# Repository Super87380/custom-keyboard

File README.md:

# Custom 75% Mechanical Keyboard

This is a custom 75% mechanical keyboard with 3 macro keys that I designed every part for, from the PCB to the firmware.

## Why I Built it
A while before finding out about Hack Club I wanted to make my own mechanical keyboard. After finding out how much it would cost I got de motivated and gave up on the idea.
Later I was watching YouTube when the creator mentioned Hack Club and how they help teenagers get experience in engineering. I was looking through the programs running when I saw KEEB.
With the opportunity to get the keyboard funded by Hack Club/KEEB it was the perfect chance for me to make the keyboard I had wanted to before.

## Features
- 3 Macro keys
- Rotary Encoder with a switch
- RGB back lighting
- Vast firmware support - the firmware I made uses KMK

## Designing
I started this project by brainstorming ideas for different layouts, sizes, and features. My original idea was a 75% keyboard with a screen, 1 macro key, and a rotary encoder. The idea soon evolved into what it is now.
After brainstorming I used [keyboard layout editor](https://www.keyboard-layout-editor.com/) and [photopea](https://www.photopea.com/) to design the layout and matrix wiring digitally.
I then made the first schematic and PCB in KiCad with a screen and 1 macro key. After I finished the schematic and PCB I realized I wanted to add backlighting for late night gaming/programming sessions and more macro keys, so I added sk6812 mini-e LED's under each switch and removed the screen for 2 more macro keys. After I finished with the electronics I designed a case and plate in Onshape, I found this pretty challenging as it was my first time using Onshape; I can definitely improve the case a lot. I then made the firmware, I chose to sue KMK because I have more expierence with python and have made a macropad with KMK already.

## What I Found Difficult
- LED wiring, especially because I didnt originally route with them in minde
- Modeling the case and plate in Onshape
- Sourcing cheap components with cheap shipping

## What I Learned
- Modelling in Onshape
- Better PCB design
- How mechanical keyboards work
- Reading data sheets and applying what I read
- Layers in KMK
- RGB in KMK

## BOM
| Sl No. | Name | Notes | Quantity | Price Per Unit | Cost | Shipping | Link |
| :---: | :--- | :--- | :---: | :---: | :---: | :---: | :--- |
| 1 | PCB | Manufactured by JLCPBC (minimum 5, order through JLclone desktop app - saves money) | 1 | $25.50 | $25.50 | $15.00 | [JLCPCB](JLCPCB) |
| 2 | Diode (1N4148) | Diodes to prevent ghosting (need 84, minimum 100) | 100 | $0.0295 | $2.95 | $13.54 | [LCSC](https://www.lcsc.com/product-detail/C258182.html) |
| 3 | Resistor (0805W8F5600T5E) | For start and end of LED data signals (only need 2, minimum of 100) | 100 | $0.0028 | $0.28 | Included* | [LCSC](https://www.lcsc.com/product-detail/C28636.html) |
| 4 | Capacitor (CC0603KRX7R7BB104) | Decoupling capacitors for LED's (need 83, multiples of 50) | 100 | $0.0142 | $1.42 | Included* | [LCSC](https://www.lcsc.com/product-detail/C108079.html?s_z=n_q_CC0603KRX7R7BB104) |
| 5 | LED (SK6812MINI-E) | LED's for backglow of the keyboard (order in multiples of 5) | 85 | $0.0651 | $5.53 | Included* | [LCSC](https://www.lcsc.com/product-detail/C5149201.html?s_z=n_SK6812%2520MINI-E) |
| 6 | Raspberry Pi Pico W (with headers) | The microcontroller for the keyboard (already owned) | 1 | $0.00 | $0.00 | $0.00 | [PiShop](https://www.pishop.ca/product/raspberry-pi-pico-w/) |
| 7 | Switches | Mechanical keyboard switches (pack of 100) | 100 | $0.20 | $20.00 | $0.00 | [Amazon](https://www.amazon.com/dp/B0CX8X1X7P) |
| 8 | Keycaps | Keycaps for the switches | 1 | $10.09 | $10.09 | $0.00 | [AliExpress](https://www.aliexpress.com/item/1005009162201589.html) |
| 9 | Rotary Encoder | Rotary encoder for volume and play/pause media (already owned) | 1 | $0.00 | $0.00 | $0.00 | [DigiKey](https://www.digikey.ca/en/products/detail/bourns-inc/PEC11R-4220F-S0012/4499661) |
| 10 | Rotary Encoder Knob | Knob for the rotary encoder, 3D printed | 1 | $0.00 | $0.00 | $0.00 | — |
| 11 | Case + plate | 3D printed | 1 | $0.00 | $0.00 | $0.00 | — |
| 12 | Stabilizers | 7x 2u, 1x 6.25u | 1 | $12.05 | $12.05 | $0.00 | [Walmart](https://www.walmart.ca/en/ip/Mechanical-Keyboard-Cherry-Mx-Switch-Pcb-Mounted-Cherry-Stabilizer-Clear-Transparent-Case-6-25U-Modifier-Key-Stabiliser/7HYKUIE7RG06) |
| 13 | USB C Cable | Aviation style, coiled | 1 | $7.56 | $7.56 | $0.00 | [Amazon](https://www.amazon.ca/Coiled-Keyboards-Aviation-Mechanical-70-87inch/dp/B0GYD7GZT2) |
| 14 | Type C to Micro USB | For connecting the USB C cable to the pico | 1 | $1.78 | $1.78 | $0.00 | [Amazon](https://www.amazon.ca/dp/B0D8ZSWC1D) |

> **Additional Notes:** Items from Amazon may have shipping charges; Amazon Prime is used so shipping costs are not included. 
> 
> All LCSC items share a combined shipping fee of **$13.54 USD**. PCB shipping is estimated at **$15.00 USD**. Total shipping: **$28.54 USD**.

- **Sub Total:** $87.16 USD
- **Shipping Total:** $28.54 USD
- **Total USD:** $115.70 USD

## Files
[PCB](PCB)
[CAD](CAD)
[Firmware](Firmware)
[Journal](JOURNAL.md)
[BOM](BOM)

## Credits
This was made possible through the funding of Hack Club and KEEB, opensource firmware and software, everyone who helped with my questions in the slack, 3D models from grabcad, tutorials on YouTube, and inspiration from other KEEB github repos.

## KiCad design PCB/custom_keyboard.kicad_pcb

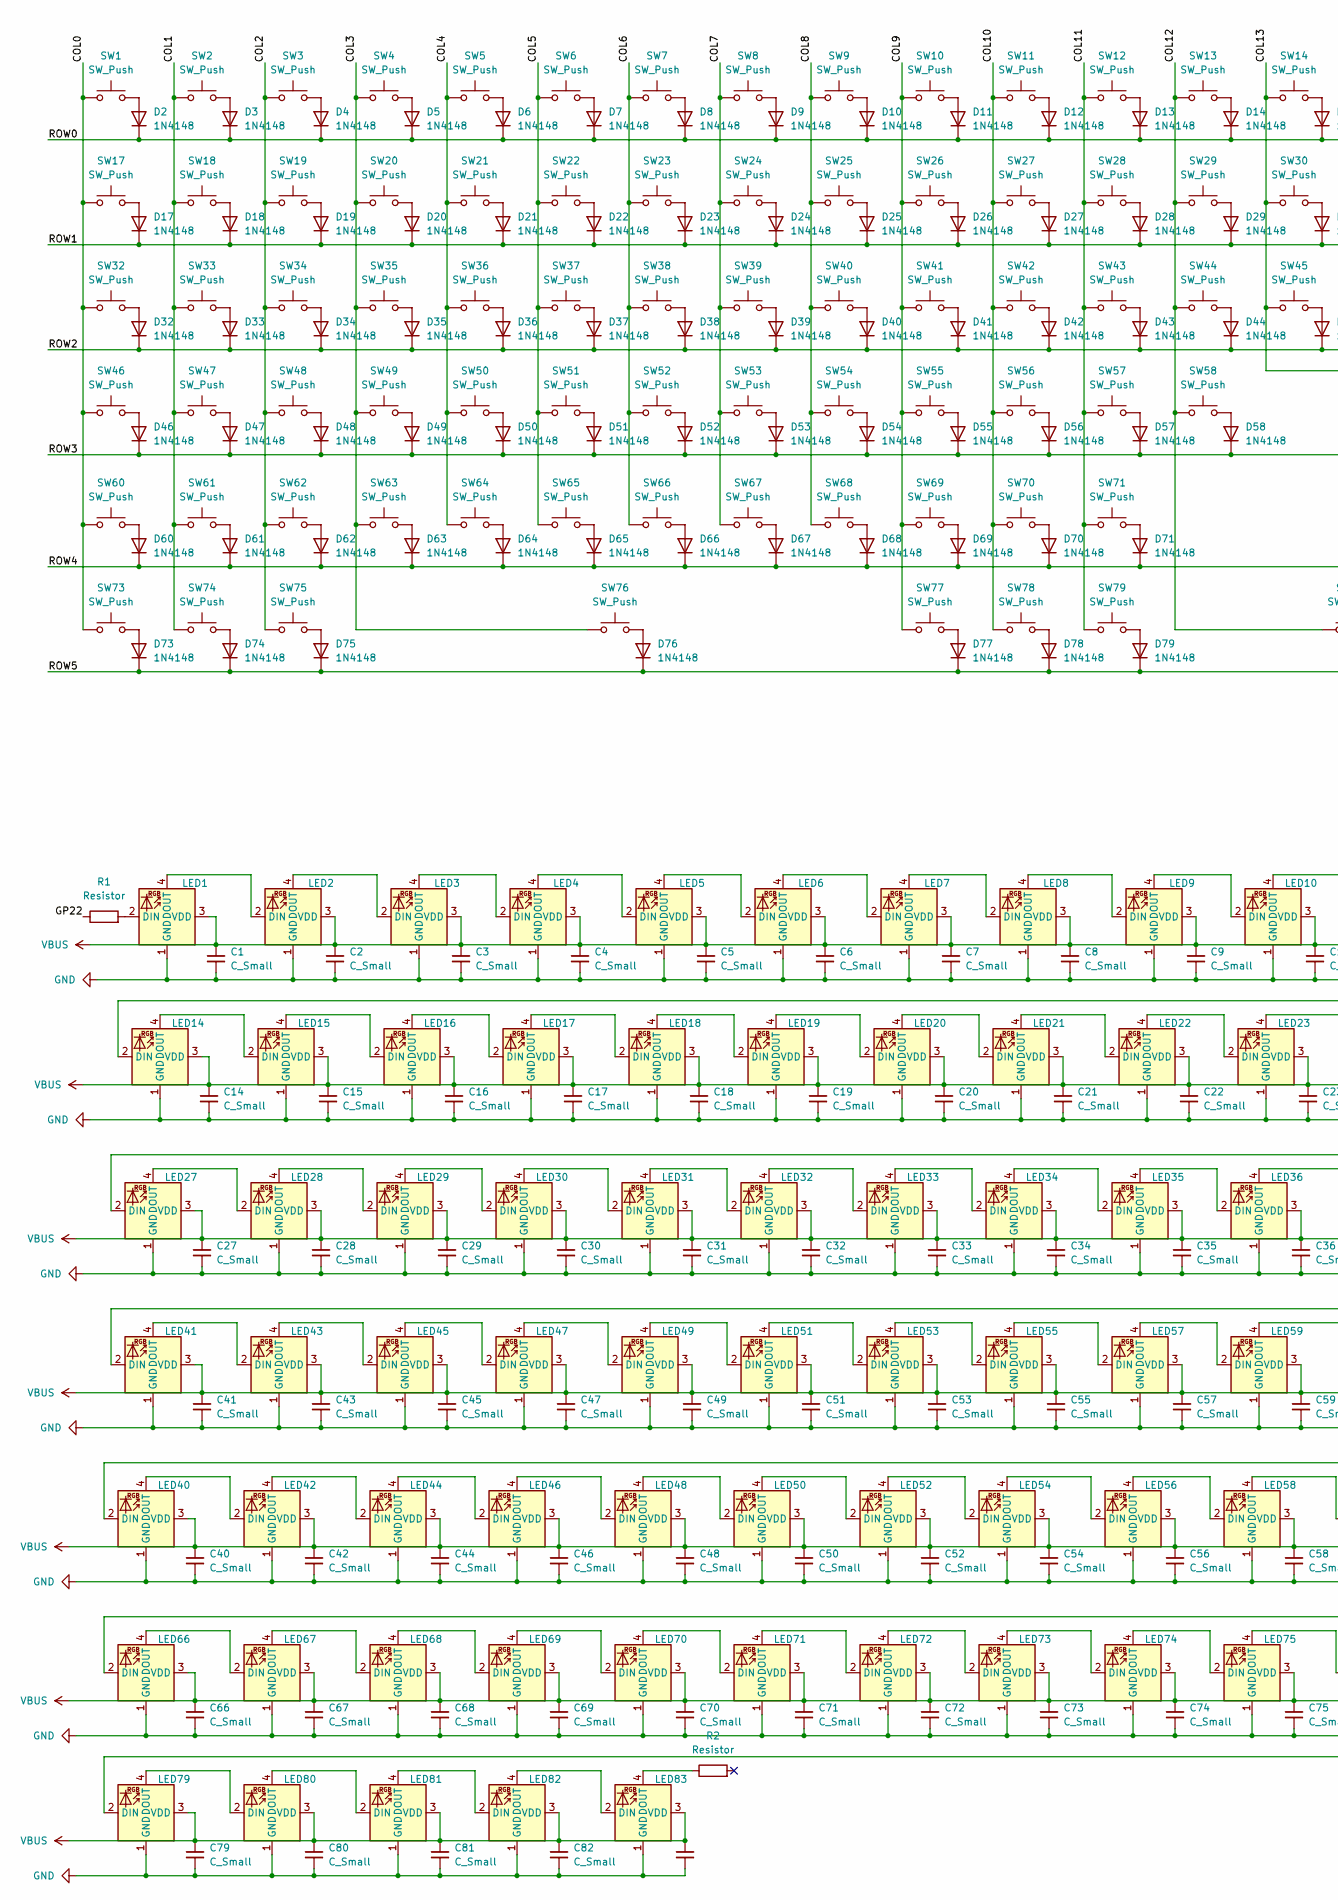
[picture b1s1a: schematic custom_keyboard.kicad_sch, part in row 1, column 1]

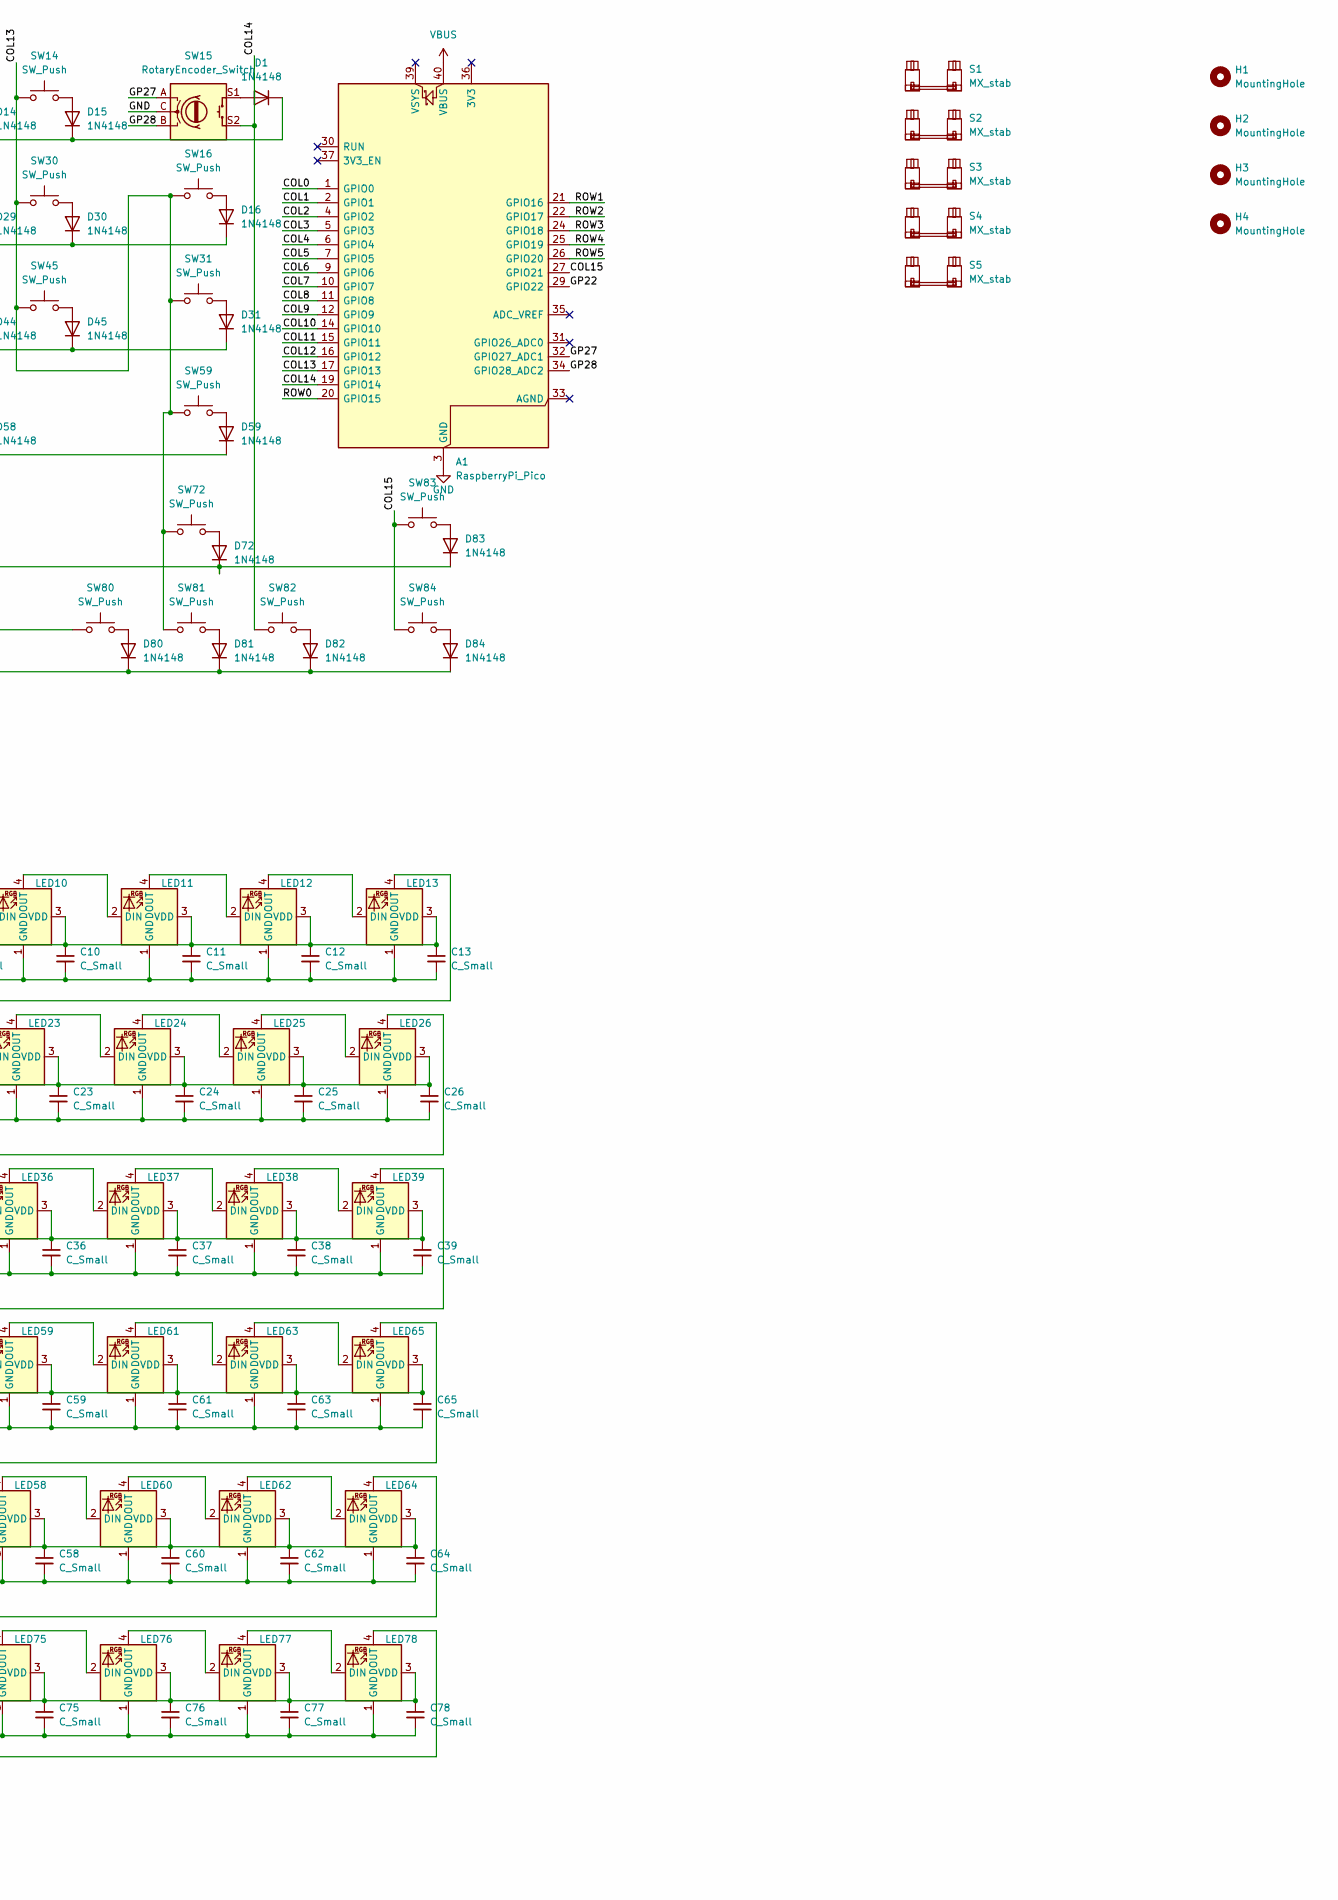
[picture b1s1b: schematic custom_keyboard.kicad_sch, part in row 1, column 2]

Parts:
A1: RaspberryPi_Pico; RaspberryPi_Pico_Common_THT
C1, C2, C3, C4, C5, C6, C7, C8, C9, C10, C11, C12, C13, C14, C15, C16, C17, C18, C19, C20, C21, C22, C23, C24, C25, C26, C27, C28, C29, C30, C31, C32, C33, C34, C35, C36, C37, C38, C39, C40, C41, C42, C43, C44, C45, C46, C47, C48, C49, C50, C51, C52, C53, C54, C55, C56, C57, C58, C59, C60, C61, C62, C63, C64, C65, C66, C67, C68, C69, C70, C71, C72, C73, C74, C75, C76, C77, C78, C79, C80, C81, C82, C83: C_Small; C_0603_1608Metric_Pad1.08x0.95mm_HandSolder
D1, D2, D3, D4, D5, D6, D7, D8, D9, D10, D11, D12, D13, D14, D15, D16, D17, D18, D19, D20, D21, D22, D23, D24, D25, D26, D27, D28, D29, D30, D31, D32, D33, D34, D35, D36, D37, D38, D39, D40, D41, D42, D43, D44, D45, D46, D47, D48, D49, D50, D51, D52, D53, D54, D55, D56, D57, D58, D59, D60, D61, D62, D63, D64, D65, D66, D67, D68, D69, D70, D71, D72, D73, D74, D75, D76, D77, D78, D79, D80, D81, D82, D83, D84: 1N4148; D_DO-35_SOD27_P7.62mm_Horizontal
H1, H2, H3, H4: MountingHole; MountingHole_3.2mm_M3_DIN965_Pad_TopBottom
LED1, LED2, LED3, LED4, LED5, LED6, LED7, LED8, LED9, LED10, LED11, LED12, LED13, LED14, LED15, LED16, LED17, LED18, LED19, LED20, LED21, LED22, LED23, LED24, LED25, LED26, LED27, LED28, LED29, LED30, LED31, LED32, LED33, LED34, LED35, LED36, LED37, LED38, LED39, LED40, LED41, LED42, LED43, LED44, LED45, LED46, LED47, LED48, LED49, LED50, LED51, LED52, LED53, LED54, LED55, LED56, LED57, LED58, LED59, LED60, LED61, LED62, LED63, LED64, LED65, LED66, LED67, LED68, LED69, LED70, LED71, LED72, LED73, LED74, LED75, LED76, LED77, LED78, LED79, LED80, LED81, LED82, LED83: MX_SK6812MINI-E_LCSC; LED_MX_6028R_1
R1, R2: Resistor; R_0805_2012Metric
S1: MX_stab; STAB_MX_2.75u_MODEL
S2, S5: MX_stab; STAB_MX_2.25u_MODEL
S3: MX_stab; STAB_MX_2u_MODEL
S4: MX_stab; STAB_MX_6.25u_MODEL
SW1, SW2, SW3, SW4, SW5, SW6, SW7, SW8, SW9, SW10, SW11, SW12, SW13, SW16, SW17, SW18, SW19, SW20, SW21, SW22, SW23, SW24, SW25, SW26, SW27, SW28, SW29, SW30, SW31, SW33, SW34, SW35, SW36, SW37, SW38, SW39, SW40, SW41, SW42, SW43, SW44, SW47, SW48, SW49, SW50, SW51, SW52, SW53, SW54, SW55, SW56, SW57, SW58, SW59, SW60, SW61, SW62, SW63, SW64, SW65, SW66, SW67, SW68, SW69, SW70, SW71, SW72, SW80, SW81, SW82, SW83, SW84: SW_Push; SW_MX_1u_MODEL
SW14, SW73, SW74, SW75, SW76, SW77, SW78: SW_Push; SW_MX_1.25u_MODEL
SW15: RotaryEncoder_Switch; ROT_Alps_EC11E-Switch
SW32, SW45, SW79: SW_Push; SW_MX_1.5u_MODEL
SW46: SW_Push; SW_MX_1.75u_MODEL

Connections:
/COL0: A1.1 (GPIO0), SW1.1, SW17.1, SW32.1, SW46.1, SW60.1, SW73.1
/COL1: A1.2 (GPIO1), SW2.1, SW18.1, SW33.1, SW47.1, SW61.1, SW74.1
/COL2: A1.4 (GPIO2), SW3.1, SW19.1, SW34.1, SW48.1, SW62.1, SW75.1
/COL3: A1.5 (GPIO3), SW4.1, SW20.1, SW35.1, SW49.1, SW63.1, SW76.1
/COL4: A1.6 (GPIO4), SW5.1, SW21.1, SW36.1, SW50.1, SW64.1
/COL5: A1.7 (GPIO5), SW6.1, SW22.1, SW37.1, SW51.1, SW65.1
/COL6: A1.9 (GPIO6), SW7.1, SW23.1, SW38.1, SW52.1, SW66.1
/COL7: A1.10 (GPIO7), SW8.1, SW24.1, SW39.1, SW53.1, SW67.1
/COL8: A1.11 (GPIO8), SW9.1, SW25.1, SW40.1, SW54.1, SW68.1
/COL9: A1.12 (GPIO9), SW10.1, SW26.1, SW41.1, SW55.1, SW69.1, SW77.1
/COL10: A1.14 (GPIO10), SW11.1, SW27.1, SW42.1, SW56.1, SW70.1, SW78.1
/COL11: A1.15 (GPIO11), SW12.1, SW28.1, SW43.1, SW57.1, SW71.1, SW79.1
/COL12: A1.16 (GPIO12), SW13.1, SW29.1, SW44.1, SW58.1, SW80.1
/COL13: A1.17 (GPIO13), SW14.1, SW16.1, SW30.1, SW31.1, SW45.1, SW59.1, SW72.1, SW81.1
/COL14: A1.19 (GPIO14), SW15.S2, SW82.1
/COL15: A1.27 (GPIO21), SW83.1, SW84.1
/GP22: A1.29 (GPIO22), R1.1
/GP27: A1.32 (GPIO27_ADC1), SW15.A
/GP28: A1.34 (GPIO28_ADC2), SW15.B
/ROW0: A1.20 (GPIO15), D1.1 (K), D2.1 (K), D3.1 (K), D4.1 (K), D5.1 (K), D6.1 (K), D7.1 (K), D8.1 (K), D9.1 (K), D10.1 (K), D11.1 (K), D12.1 (K), D13.1 (K), D14.1 (K), D15.1 (K)
/ROW1: A1.21 (GPIO16), D16.1 (K), D17.1 (K), D18.1 (K), D19.1 (K), D20.1 (K), D21.1 (K), D22.1 (K), D23.1 (K), D24.1 (K), D25.1 (K), D26.1 (K), D27.1 (K), D28.1 (K), D29.1 (K), D30.1 (K)
/ROW2: A1.22 (GPIO17), D31.1 (K), D32.1 (K), D33.1 (K), D34.1 (K), D35.1 (K), D36.1 (K), D37.1 (K), D38.1 (K), D39.1 (K), D40.1 (K), D41.1 (K), D42.1 (K), D43.1 (K), D44.1 (K), D45.1 (K)
/ROW3: A1.24 (GPIO18), D46.1 (K), D47.1 (K), D48.1 (K), D49.1 (K), D50.1 (K), D51.1 (K), D52.1 (K), D53.1 (K), D54.1 (K), D55.1 (K), D56.1 (K), D57.1 (K), D58.1 (K), D59.1 (K)
/ROW4: A1.25 (GPIO19), D60.1 (K), D61.1 (K), D62.1 (K), D63.1 (K), D64.1 (K), D65.1 (K), D66.1 (K), D67.1 (K), D68.1 (K), D69.1 (K), D70.1 (K), D71.1 (K), D72.1 (K), D83.1 (K)
/ROW5: A1.26 (GPIO20), D73.1 (K), D74.1 (K), D75.1 (K), D76.1 (K), D77.1 (K), D78.1 (K), D79.1 (K), D80.1 (K), D81.1 (K), D82.1 (K), D84.1 (K)
GND: A1.3 (GND), A1.8 (GND), A1.13 (GND), A1.18 (GND), A1.23 (GND), A1.28 (GND), A1.38 (GND), C1.2, C2.2, C3.2, C4.2, C5.2, C6.2, C7.2, C8.2, C9.2, C10.2, C11.2, C12.2, C13.2, C14.2, C15.2, C16.2, C17.2, C18.2, C19.2, C20.2, C21.2, C22.2, C23.2, C24.2, C25.2, C26.2, C27.2, C28.2, C29.2, C30.2, C31.2, C32.2, C33.2, C34.2, C35.2, C36.2, C37.2, C38.2, C39.2, C40.2, C41.2, C42.2, C43.2, C44.2, C45.2, C46.2, C47.2, C48.2, C49.2, C50.2, C51.2, C52.2, C53.2, C54.2, C55.2, C56.2, C57.2, C58.2, C59.2, C60.2, C61.2, C62.2, C63.2, C64.2, C65.2, C66.2, C67.2, C68.2, C69.2, C70.2, C71.2, C72.2, C73.2, C74.2, C75.2, C76.2, C77.2, C78.2, C79.2, C80.2, C81.2, C82.2, C83.2, LED1.1 (GND), LED2.1 (GND), LED3.1 (GND), LED4.1 (GND), LED5.1 (GND), LED6.1 (GND), LED7.1 (GND), LED8.1 (GND), LED9.1 (GND), LED10.1 (GND), LED11.1 (GND), LED12.1 (GND), LED13.1 (GND), LED14.1 (GND), LED15.1 (GND), LED16.1 (GND), LED17.1 (GND), LED18.1 (GND), LED19.1 (GND), LED20.1 (GND), LED21.1 (GND), LED22.1 (GND), LED23.1 (GND), LED24.1 (GND), LED25.1 (GND), LED26.1 (GND), LED27.1 (GND), LED28.1 (GND), LED29.1 (GND), LED30.1 (GND), LED31.1 (GND), LED32.1 (GND), LED33.1 (GND), LED34.1 (GND), LED35.1 (GND), LED36.1 (GND), LED37.1 (GND), LED38.1 (GND), LED39.1 (GND), LED40.1 (GND), LED41.1 (GND), LED42.1 (GND), LED43.1 (GND), LED44.1 (GND), LED45.1 (GND), LED46.1 (GND), LED47.1 (GND), LED48.1 (GND), LED49.1 (GND), LED50.1 (GND), LED51.1 (GND), LED52.1 (GND), LED53.1 (GND), LED54.1 (GND), LED55.1 (GND), LED56.1 (GND), LED57.1 (GND), LED58.1 (GND), LED59.1 (GND), LED60.1 (GND), LED61.1 (GND), LED62.1 (GND), LED63.1 (GND), LED64.1 (GND), LED65.1 (GND), LED66.1 (GND), LED67.1 (GND), LED68.1 (GND), LED69.1 (GND), LED70.1 (GND), LED71.1 (GND), LED72.1 (GND), LED73.1 (GND), LED74.1 (GND), LED75.1 (GND), LED76.1 (GND), LED77.1 (GND), LED78.1 (GND), LED79.1 (GND), LED80.1 (GND), LED81.1 (GND), LED82.1 (GND), LED83.1 (GND), SW15.C
unnamed: D1.2 (A), SW15.S1
unnamed: D2.2 (A), SW1.2
unnamed: D3.2 (A), SW2.2
unnamed: D4.2 (A), SW3.2
unnamed: D5.2 (A), SW4.2
unnamed: D6.2 (A), SW5.2
unnamed: D7.2 (A), SW6.2
unnamed: D8.2 (A), SW7.2
unnamed: D9.2 (A), SW8.2
unnamed: D10.2 (A), SW9.2
unnamed: D11.2 (A), SW10.2
unnamed: D12.2 (A), SW11.2
unnamed: D13.2 (A), SW12.2
unnamed: D14.2 (A), SW13.2
unnamed: D15.2 (A), SW14.2
unnamed: D16.2 (A), SW16.2
unnamed: D17.2 (A), SW17.2
unnamed: D18.2 (A), SW18.2
unnamed: D19.2 (A), SW19.2
unnamed: D20.2 (A), SW20.2
unnamed: D21.2 (A), SW21.2
unnamed: D22.2 (A), SW22.2
unnamed: D23.2 (A), SW23.2
unnamed: D24.2 (A), SW24.2
unnamed: D25.2 (A), SW25.2
unnamed: D26.2 (A), SW26.2
unnamed: D27.2 (A), SW27.2
unnamed: D28.2 (A), SW28.2
unnamed: D29.2 (A), SW29.2
unnamed: D30.2 (A), SW30.2
unnamed: D31.2 (A), SW31.2
unnamed: D32.2 (A), SW32.2
unnamed: D33.2 (A), SW33.2
unnamed: D34.2 (A), SW34.2
unnamed: D35.2 (A), SW35.2
unnamed: D36.2 (A), SW36.2
unnamed: D37.2 (A), SW37.2
unnamed: D38.2 (A), SW38.2
unnamed: D39.2 (A), SW39.2
unnamed: D40.2 (A), SW40.2
unnamed: D41.2 (A), SW41.2
unnamed: D42.2 (A), SW42.2
unnamed: D43.2 (A), SW43.2
unnamed: D44.2 (A), SW44.2
unnamed: D45.2 (A), SW45.2
unnamed: D46.2 (A), SW46.2
unnamed: D47.2 (A), SW47.2
unnamed: D48.2 (A), SW48.2
unnamed: D49.2 (A), SW49.2
unnamed: D50.2 (A), SW50.2
unnamed: D51.2 (A), SW51.2
unnamed: D52.2 (A), SW52.2
unnamed: D53.2 (A), SW53.2
unnamed: D54.2 (A), SW54.2
unnamed: D55.2 (A), SW55.2
unnamed: D56.2 (A), SW56.2
unnamed: D57.2 (A), SW57.2
unnamed: D58.2 (A), SW58.2
unnamed: D59.2 (A), SW59.2
unnamed: D60.2 (A), SW60.2
unnamed: D61.2 (A), SW61.2
unnamed: D62.2 (A), SW62.2
unnamed: D63.2 (A), SW63.2
unnamed: D64.2 (A), SW64.2
unnamed: D65.2 (A), SW65.2
unnamed: D66.2 (A), SW66.2
unnamed: D67.2 (A), SW67.2
unnamed: D68.2 (A), SW68.2
unnamed: D69.2 (A), SW69.2
unnamed: D70.2 (A), SW70.2
unnamed: D71.2 (A), SW71.2
unnamed: D72.2 (A), SW72.2
unnamed: D73.2 (A), SW73.2
unnamed: D74.2 (A), SW74.2
unnamed: D75.2 (A), SW75.2
unnamed: D76.2 (A), SW76.2
unnamed: D77.2 (A), SW77.2
unnamed: D78.2 (A), SW78.2
unnamed: D79.2 (A), SW79.2
unnamed: D80.2 (A), SW80.2
unnamed: D81.2 (A), SW81.2
unnamed: D82.2 (A), SW82.2
unnamed: D83.2 (A), SW83.2
unnamed: D84.2 (A), SW84.2
unnamed: LED1.2 (DIN), R1.2
unnamed: LED1.4 (DOUT), LED2.2 (DIN)
unnamed: LED2.4 (DOUT), LED3.2 (DIN)
unnamed: LED3.4 (DOUT), LED4.2 (DIN)
unnamed: LED4.4 (DOUT), LED5.2 (DIN)
unnamed: LED5.4 (DOUT), LED6.2 (DIN)
unnamed: LED6.4 (DOUT), LED7.2 (DIN)
unnamed: LED7.4 (DOUT), LED8.2 (DIN)
unnamed: LED8.4 (DOUT), LED9.2 (DIN)
unnamed: LED9.4 (DOUT), LED10.2 (DIN)
unnamed: LED10.4 (DOUT), LED11.2 (DIN)
unnamed: LED11.4 (DOUT), LED12.2 (DIN)
unnamed: LED12.4 (DOUT), LED13.2 (DIN)
unnamed: LED13.4 (DOUT), LED14.2 (DIN)
unnamed: LED14.4 (DOUT), LED15.2 (DIN)
unnamed: LED15.4 (DOUT), LED16.2 (DIN)
unnamed: LED16.4 (DOUT), LED17.2 (DIN)
unnamed: LED17.4 (DOUT), LED18.2 (DIN)
unnamed: LED18.4 (DOUT), LED19.2 (DIN)
unnamed: LED19.4 (DOUT), LED20.2 (DIN)
unnamed: LED20.4 (DOUT), LED21.2 (DIN)
unnamed: LED21.4 (DOUT), LED22.2 (DIN)
unnamed: LED22.4 (DOUT), LED23.2 (DIN)
unnamed: LED23.4 (DOUT), LED24.2 (DIN)
unnamed: LED24.4 (DOUT), LED25.2 (DIN)
unnamed: LED25.4 (DOUT), LED26.2 (DIN)
unnamed: LED26.4 (DOUT), LED27.2 (DIN)
unnamed: LED27.4 (DOUT), LED28.2 (DIN)
unnamed: LED28.4 (DOUT), LED29.2 (DIN)
unnamed: LED29.4 (DOUT), LED30.2 (DIN)
unnamed: LED30.4 (DOUT), LED31.2 (DIN)
unnamed: LED31.4 (DOUT), LED32.2 (DIN)
unnamed: LED32.4 (DOUT), LED33.2 (DIN)
unnamed: LED33.4 (DOUT), LED34.2 (DIN)
unnamed: LED34.4 (DOUT), LED35.2 (DIN)
unnamed: LED35.4 (DOUT), LED36.2 (DIN)
unnamed: LED36.4 (DOUT), LED37.2 (DIN)
unnamed: LED37.4 (DOUT), LED38.2 (DIN)
unnamed: LED38.4 (DOUT), LED39.2 (DIN)
unnamed: LED39.4 (DOUT), LED41.2 (DIN)
unnamed: LED40.2 (DIN), LED65.4 (DOUT)
unnamed: LED40.4 (DOUT), LED42.2 (DIN)
unnamed: LED41.4 (DOUT), LED43.2 (DIN)
unnamed: LED42.4 (DOUT), LED44.2 (DIN)
unnamed: LED43.4 (DOUT), LED45.2 (DIN)
unnamed: LED44.4 (DOUT), LED46.2 (DIN)
unnamed: LED45.4 (DOUT), LED47.2 (DIN)
unnamed: LED46.4 (DOUT), LED48.2 (DIN)
unnamed: LED47.4 (DOUT), LED49.2 (DIN)
unnamed: LED48.4 (DOUT), LED50.2 (DIN)
unnamed: LED49.4 (DOUT), LED51.2 (DIN)
unnamed: LED50.4 (DOUT), LED52.2 (DIN)
unnamed: LED51.4 (DOUT), LED53.2 (DIN)
unnamed: LED52.4 (DOUT), LED54.2 (DIN)
unnamed: LED53.4 (DOUT), LED55.2 (DIN)
unnamed: LED54.4 (DOUT), LED56.2 (DIN)
unnamed: LED55.4 (DOUT), LED57.2 (DIN)
unnamed: LED56.4 (DOUT), LED58.2 (DIN)
unnamed: LED57.4 (DOUT), LED59.2 (DIN)
unnamed: LED58.4 (DOUT), LED60.2 (DIN)
unnamed: LED59.4 (DOUT), LED61.2 (DIN)
unnamed: LED60.4 (DOUT), LED62.2 (DIN)
unnamed: LED61.4 (DOUT), LED63.2 (DIN)
unnamed: LED62.4 (DOUT), LED64.2 (DIN)
unnamed: LED63.4 (DOUT), LED65.2 (DIN)
unnamed: LED64.4 (DOUT), LED66.2 (DIN)
unnamed: LED66.4 (DOUT), LED67.2 (DIN)
unnamed: LED67.4 (DOUT), LED68.2 (DIN)
unnamed: LED68.4 (DOUT), LED69.2 (DIN)
unnamed: LED69.4 (DOUT), LED70.2 (DIN)
unnamed: LED70.4 (DOUT), LED71.2 (DIN)
unnamed: LED71.4 (DOUT), LED72.2 (DIN)
unnamed: LED72.4 (DOUT), LED73.2 (DIN)
unnamed: LED73.4 (DOUT), LED74.2 (DIN)
unnamed: LED74.4 (DOUT), LED75.2 (DIN)
unnamed: LED75.4 (DOUT), LED76.2 (DIN)
unnamed: LED76.4 (DOUT), LED77.2 (DIN)
unnamed: LED77.4 (DOUT), LED78.2 (DIN)
unnamed: LED78.4 (DOUT), LED79.2 (DIN)
unnamed: LED79.4 (DOUT), LED80.2 (DIN)
unnamed: LED80.4 (DOUT), LED81.2 (DIN)
unnamed: LED81.4 (DOUT), LED82.2 (DIN)
unnamed: LED82.4 (DOUT), LED83.2 (DIN)
unnamed: LED83.4 (DOUT), R2.1
VBUS: A1.40 (VBUS), C1.1, C2.1, C3.1, C4.1, C5.1, C6.1, C7.1, C8.1, C9.1, C10.1, C11.1, C12.1, C13.1, C14.1, C15.1, C16.1, C17.1, C18.1, C19.1, C20.1, C21.1, C22.1, C23.1, C24.1, C25.1, C26.1, C27.1, C28.1, C29.1, C30.1, C31.1, C32.1, C33.1, C34.1, C35.1, C36.1, C37.1, C38.1, C39.1, C40.1, C41.1, C42.1, C43.1, C44.1, C45.1, C46.1, C47.1, C48.1, C49.1, C50.1, C51.1, C52.1, C53.1, C54.1, C55.1, C56.1, C57.1, C58.1, C59.1, C60.1, C61.1, C62.1, C63.1, C64.1, C65.1, C66.1, C67.1, C68.1, C69.1, C70.1, C71.1, C72.1, C73.1, C74.1, C75.1, C76.1, C77.1, C78.1, C79.1, C80.1, C81.1, C82.1, C83.1, LED1.3 (VDD), LED2.3 (VDD), LED3.3 (VDD), LED4.3 (VDD), LED5.3 (VDD), LED6.3 (VDD), LED7.3 (VDD), LED8.3 (VDD), LED9.3 (VDD), LED10.3 (VDD), LED11.3 (VDD), LED12.3 (VDD), LED13.3 (VDD), LED14.3 (VDD), LED15.3 (VDD), LED16.3 (VDD), LED17.3 (VDD), LED18.3 (VDD), LED19.3 (VDD), LED20.3 (VDD), LED21.3 (VDD), LED22.3 (VDD), LED23.3 (VDD), LED24.3 (VDD), LED25.3 (VDD), LED26.3 (VDD), LED27.3 (VDD), LED28.3 (VDD), LED29.3 (VDD), LED30.3 (VDD), LED31.3 (VDD), LED32.3 (VDD), LED33.3 (VDD), LED34.3 (VDD), LED35.3 (VDD), LED36.3 (VDD), LED37.3 (VDD), LED38.3 (VDD), LED39.3 (VDD), LED40.3 (VDD), LED41.3 (VDD), LED42.3 (VDD), LED43.3 (VDD), LED44.3 (VDD), LED45.3 (VDD), LED46.3 (VDD), LED47.3 (VDD), LED48.3 (VDD), LED49.3 (VDD), LED50.3 (VDD), LED51.3 (VDD), LED52.3 (VDD), LED53.3 (VDD), LED54.3 (VDD), LED55.3 (VDD), LED56.3 (VDD), LED57.3 (VDD), LED58.3 (VDD), LED59.3 (VDD), LED60.3 (VDD), LED61.3 (VDD), LED62.3 (VDD), LED63.3 (VDD), LED64.3 (VDD), LED65.3 (VDD), LED66.3 (VDD), LED67.3 (VDD), LED68.3 (VDD), LED69.3 (VDD), LED70.3 (VDD), LED71.3 (VDD), LED72.3 (VDD), LED73.3 (VDD), LED74.3 (VDD), LED75.3 (VDD), LED76.3 (VDD), LED77.3 (VDD), LED78.3 (VDD), LED79.3 (VDD), LED80.3 (VDD), LED81.3 (VDD), LED82.3 (VDD), LED83.3 (VDD)

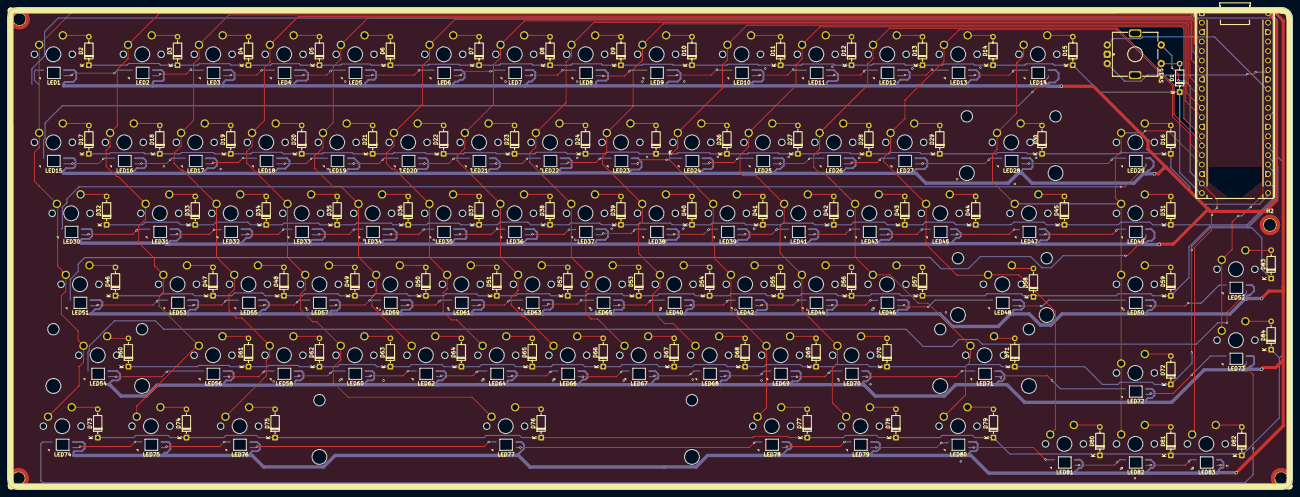
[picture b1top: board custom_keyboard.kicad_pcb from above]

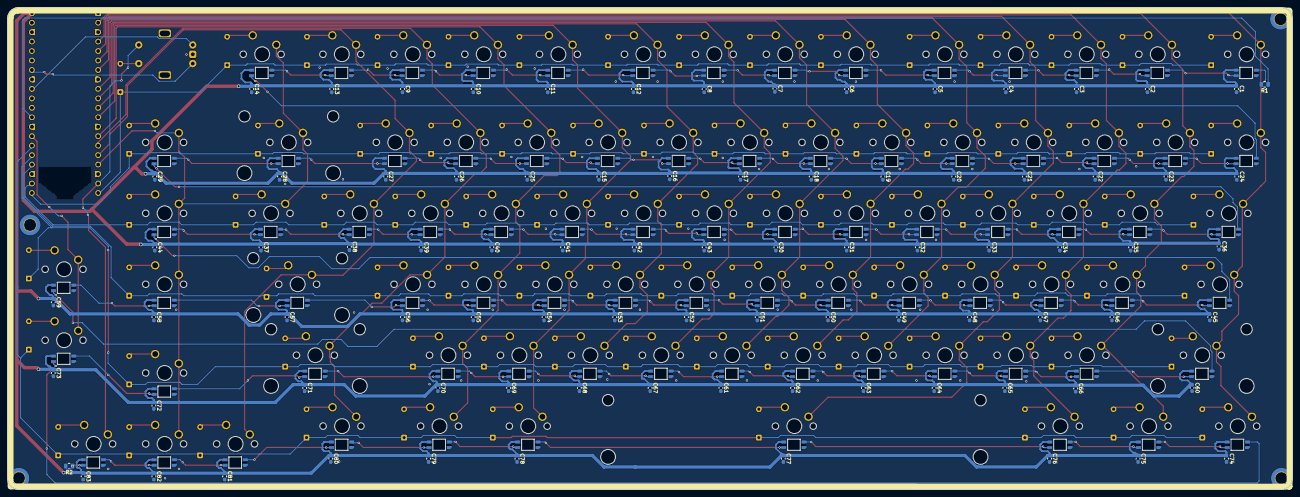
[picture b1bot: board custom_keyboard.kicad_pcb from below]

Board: 2 copper layers, 345.0 x 129.4 mm, 346 parts (85 on the bottom side), 195 nets.
